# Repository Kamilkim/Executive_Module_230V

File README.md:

# Executive_Module_230V
Executive module to controll devices on voltage 230V

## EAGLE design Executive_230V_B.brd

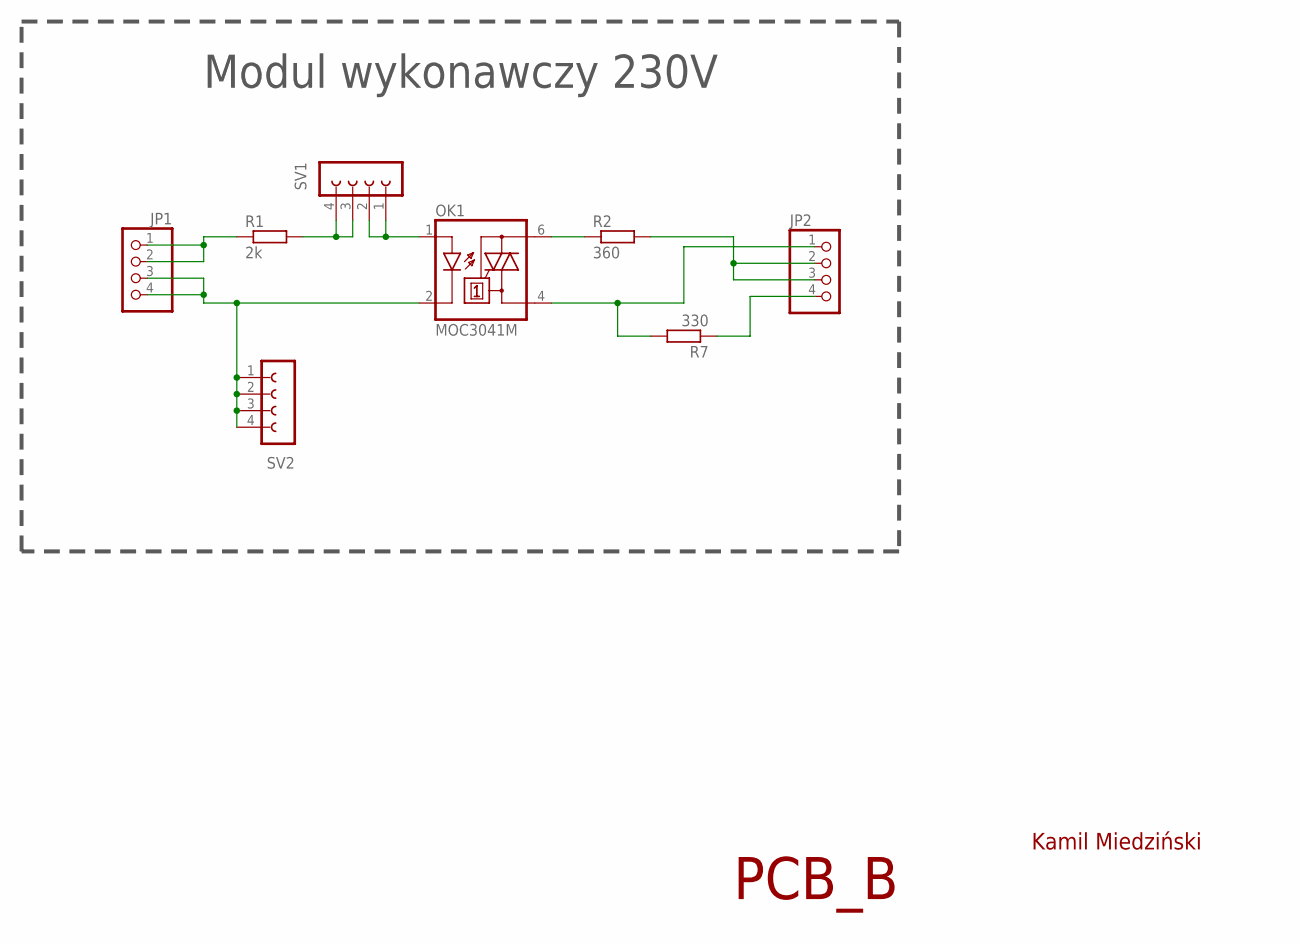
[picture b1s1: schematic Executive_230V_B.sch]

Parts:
JP1, JP2: PINHD-1X41X04H; 1X04H
OK1: MOC3041M; DIL06
R1: 2k; 0207/10
R2: 360; 0207/10; MPN MFR4-360RFI
R7: 330; 0207/10
SV1, SV2: FE04-1

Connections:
unnamed: JP1.3, JP1.4, OK1.2 (C), SV2.1 (2), SV2.2 (3), SV2.3 (4), SV2.4 (5)
unnamed: JP1.1, JP1.2, R1.1
unnamed: R1.2, SV1.3 (4), SV1.4 (5)
unnamed: OK1.1 (A), SV1.1 (2), SV1.2 (3)
unnamed: OK1.6 (A2), R2.1
unnamed: JP2.4, R7.1
unnamed: JP2.1, OK1.4 (A1), R7.2
unnamed: JP2.2, JP2.3, R2.2

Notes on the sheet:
Kamil Miedziński
Modul wykonawczy 230V
PCB_B

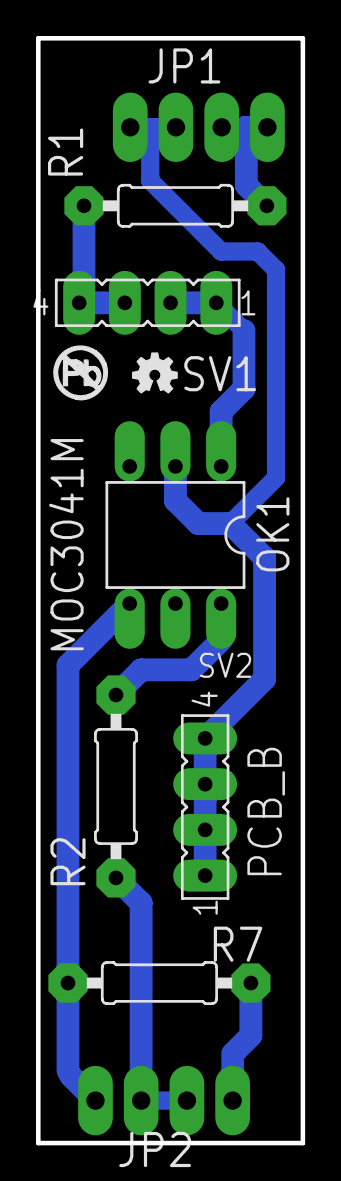
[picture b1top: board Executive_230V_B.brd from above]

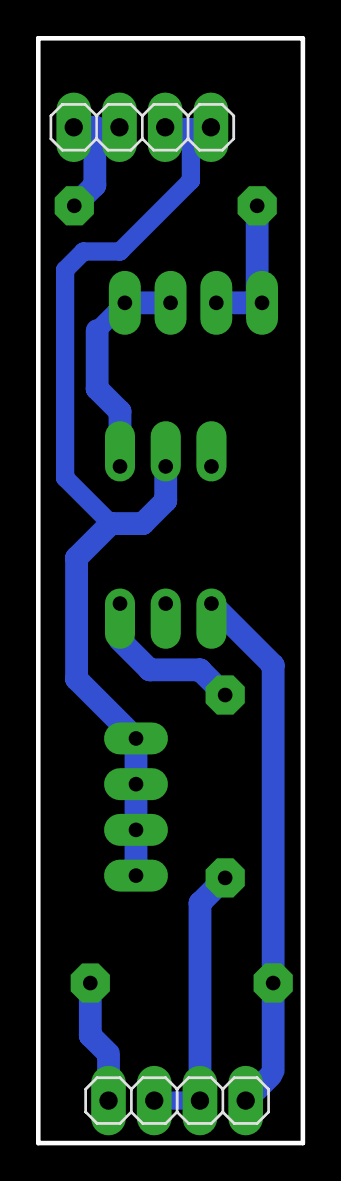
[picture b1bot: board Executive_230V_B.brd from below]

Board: 2 copper layers, 14.7 x 61.4 mm, 10 parts (2 on the bottom side), 8 nets.

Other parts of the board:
U$1: OSHW-LOGO-MINI
U$2: NO_PB_LOGO_0.120

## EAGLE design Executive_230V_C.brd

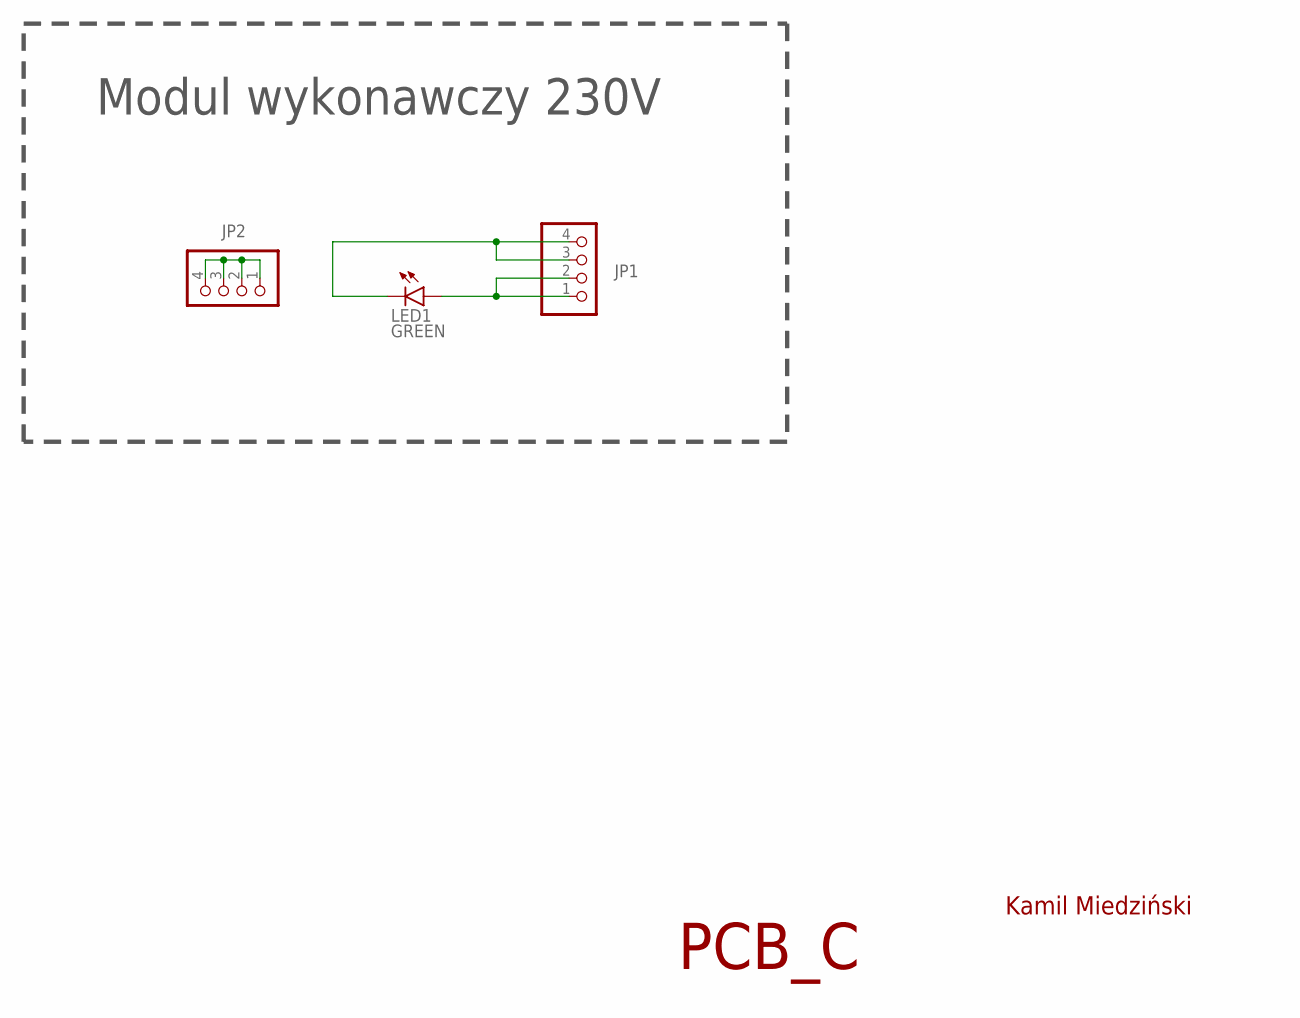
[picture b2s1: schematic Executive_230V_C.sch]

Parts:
JP1, JP2: PINHD-1X41X04H; 1X04H
LED1: GREEN; LED5MM_GREEN

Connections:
unnamed: JP1.1, JP1.2, LED1.A
unnamed: JP1.3, JP1.4, LED1.K (C)
unnamed: JP2.1, JP2.2, JP2.3, JP2.4

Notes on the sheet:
Kamil Miedziński
Modul wykonawczy 230V
PCB_C

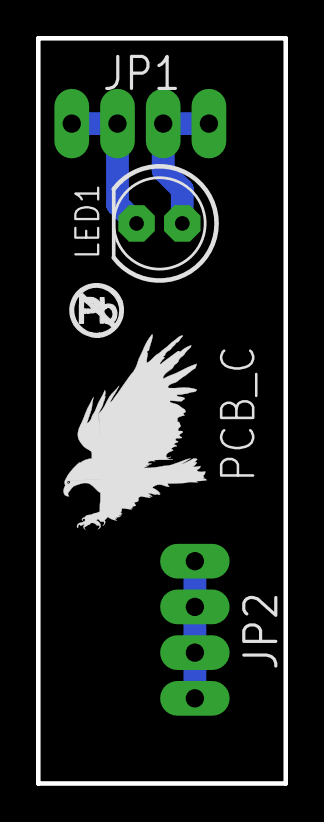
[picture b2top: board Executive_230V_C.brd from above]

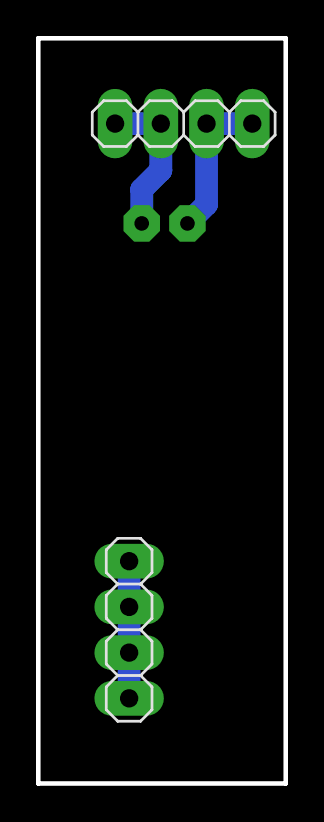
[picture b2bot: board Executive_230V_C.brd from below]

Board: 2 copper layers, 13.7 x 41.4 mm, 5 parts (2 on the bottom side), 3 nets.

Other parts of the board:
U$1: EAGLE-PLC-8MM
U$2: NO_PB_LOGO_0.120

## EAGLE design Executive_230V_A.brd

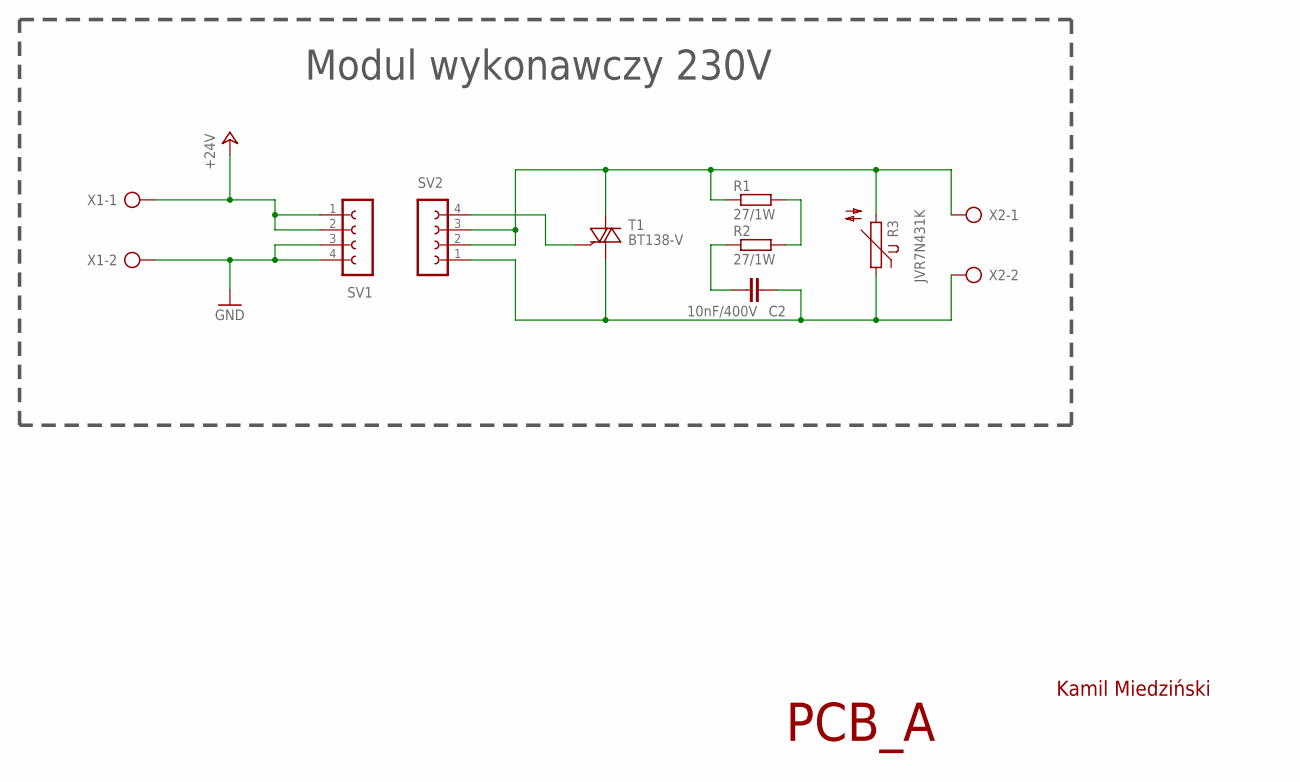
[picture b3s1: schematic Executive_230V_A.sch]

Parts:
C2: 10nF/400V; C102-054X133
R1, R2: 27/1W; 0411/15
R3: JVR7N431K; S05K11
SV1, SV2: FE04-1
T1: BT138-V; TO220BV
X1, X2: GMKDSP_3/2

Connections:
+24V: SV1.1 (2), SV1.2 (3), X1.1
GND: SV1.3 (4), SV1.4 (5), X1.2
unnamed: C2.1, R2.1
unnamed: R1.2, R2.2
unnamed: SV2.4 (5), T1.G
unnamed: C2.2, R3.1, SV2.1 (2), T1.T1 (A1), X2.2
unnamed: R1.1, R3.2, SV2.2 (3), SV2.3 (4), T1.T2 (A2), X2.1

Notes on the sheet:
Kamil Miedziński
Modul wykonawczy 230V
PCB_A

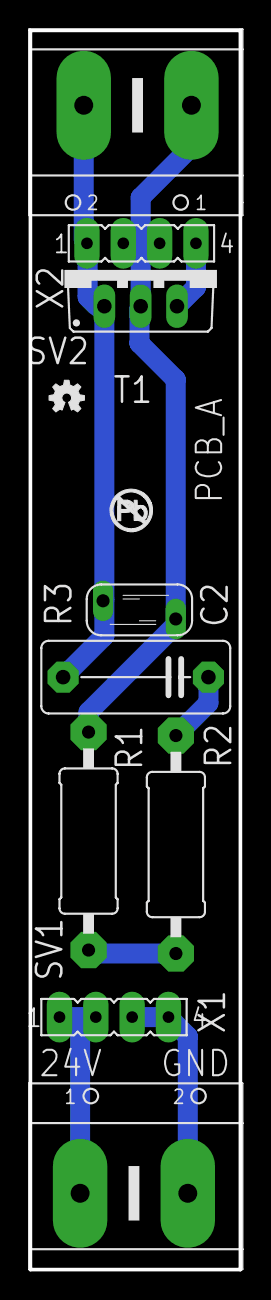
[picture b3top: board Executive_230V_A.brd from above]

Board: 2 copper layers, 14.7 x 86.6 mm, 11 parts (0 on the bottom side), 7 nets.

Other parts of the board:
U$1: NO_PB_LOGO_0.120
U$2: OSHW-LOGO-MINI

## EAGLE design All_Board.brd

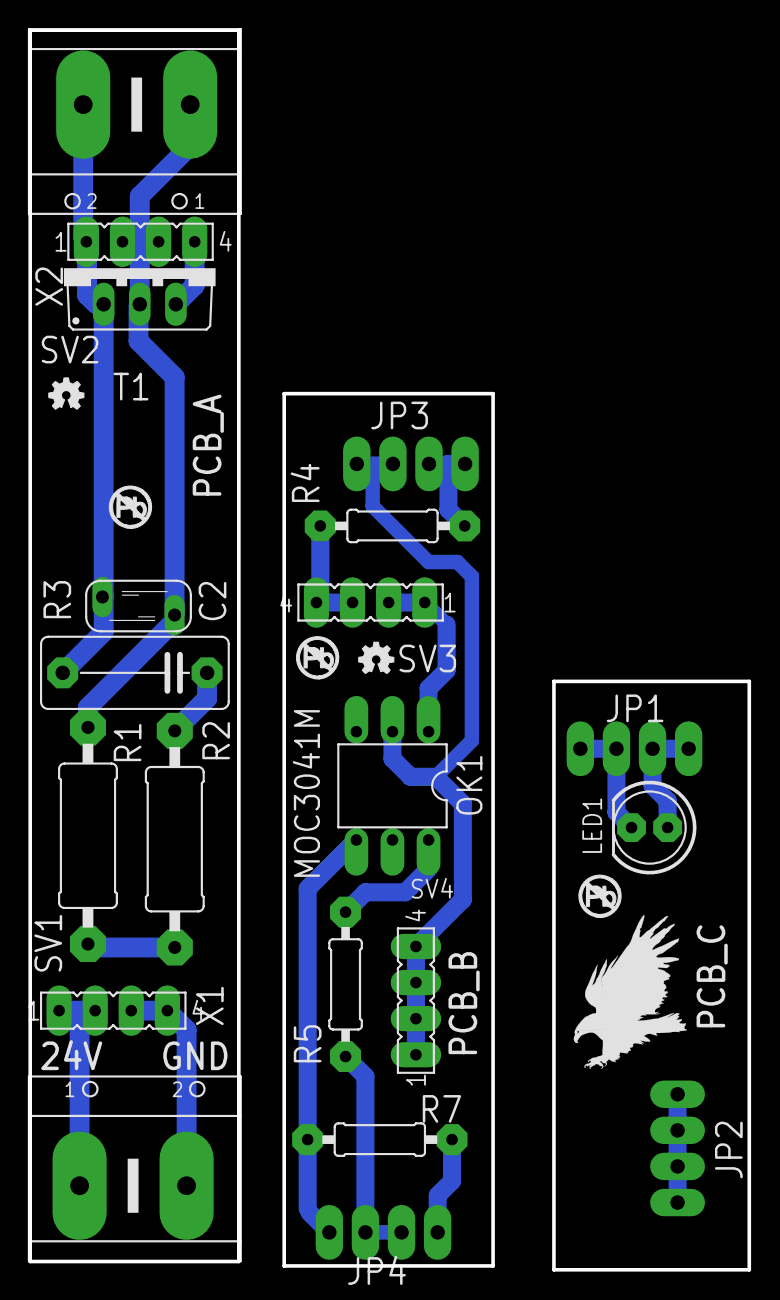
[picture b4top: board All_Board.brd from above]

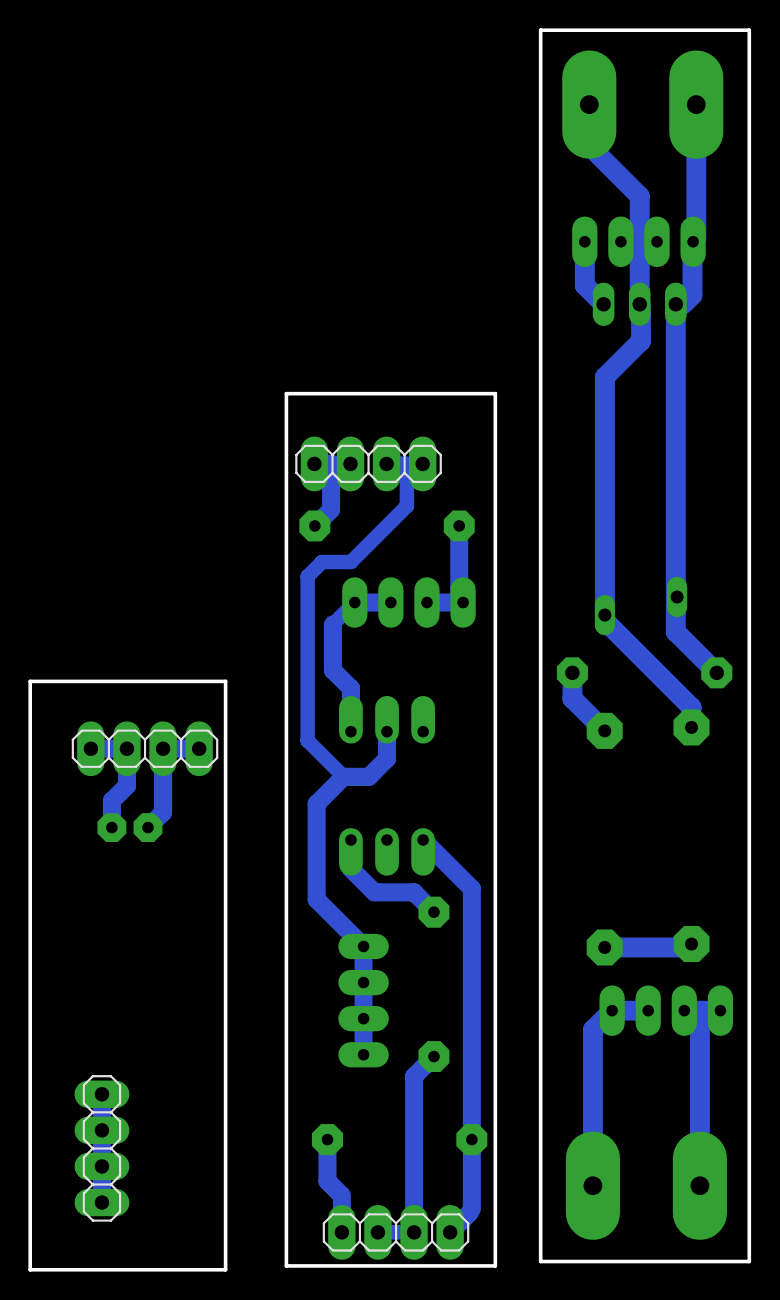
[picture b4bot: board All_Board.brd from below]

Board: 2 copper layers, 50.6 x 87.2 mm, 26 parts (4 on the bottom side), 18 nets.

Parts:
C2: 10nF/400V; C102-054X133
JP1, JP2, JP3, JP4: 1X04H
LED1: GREEN; LED5MM_GREEN
OK1: MOC3041M; DIL06
R1, R2: 27/1W; 0411/15
R3: JVR7N431K; S05K11
R4: 2k; 0207/10
R5: 360; 0207/10
R7: 330; 0207/10
SV1, SV2, SV3, SV4: FE04-1
T1: BT138-V; TO220BV
U$1: EAGLE-PLC-8MM
U$2, U$3, U$6: NO_PB_LOGO_0.120
U$4, U$5: OSHW-LOGO-MINI
X1, X2: GMKDSP_3/2

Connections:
+24V: SV1.1, SV1.2, X1.1
GND: SV1.3, SV1.4, X1.2
unnamed: JP1.1, JP1.2, LED1.A
unnamed: JP1.3, JP1.4, LED1.K
unnamed: C2.2, R3.1, SV2.1, T1.T1, X2.2
unnamed: JP2.1, JP2.2, JP2.3, JP2.4
unnamed: SV2.4, T1.G
unnamed: C2.1, R2.1
unnamed: R1.1, R3.2, SV2.2, SV2.3, T1.T2, X2.1
unnamed: R1.2, R2.2
unnamed: R4.2, SV3.3, SV3.4
unnamed: OK1.1, SV3.1, SV3.2
unnamed: OK1.6, R5.1
unnamed: JP4.1, OK1.4, R7.2
unnamed: JP3.1, JP3.2, R4.1
unnamed: JP3.3, JP3.4, OK1.2, SV4.1, SV4.2, SV4.3, SV4.4
unnamed: JP4.2, JP4.3, R5.2
unnamed: JP4.4, R7.1

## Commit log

2019-11-09 Image

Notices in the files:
parts and their libraries:
SparkFun-Aesthetics: Licensing: Creative Commons ShareAlike 4.0 International - https://creativecommons.org/licenses/by-sa/4.0
